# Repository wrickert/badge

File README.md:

<h2> BSidesIowa 2019 Badge </h2>
The badge for BSidesIowa 2019 conference is a penny piano running on an ESP32 microcontroller running micropython.
This badge is fully rechargeable and all that is required to program it is a micro usb cable. 

<h3> Micropython </h3>
The micropython REPL prompt can be accessed using a serial console running at 115200 baud. 
Documentation for micropython can be found here, https://docs.micropython.org/en/latest/esp32/quickref.html

<h3> To program </h3>
The badge can be programmed directly through the REPL prompt on the serial console. To load new files onto the ESP32, first access the serial console and press Ctrl+C to end the running program on the board. Then, exit the serial console and use ampy.py to load new programs. Instructions to install ampy can be found here, https://learn.adafruit.com/micropython-basics-load-files-and-run-code/install-ampy

Common ampy commands:<br>
To program the board: ampy -p /dev/ttyUSB0 put main.py

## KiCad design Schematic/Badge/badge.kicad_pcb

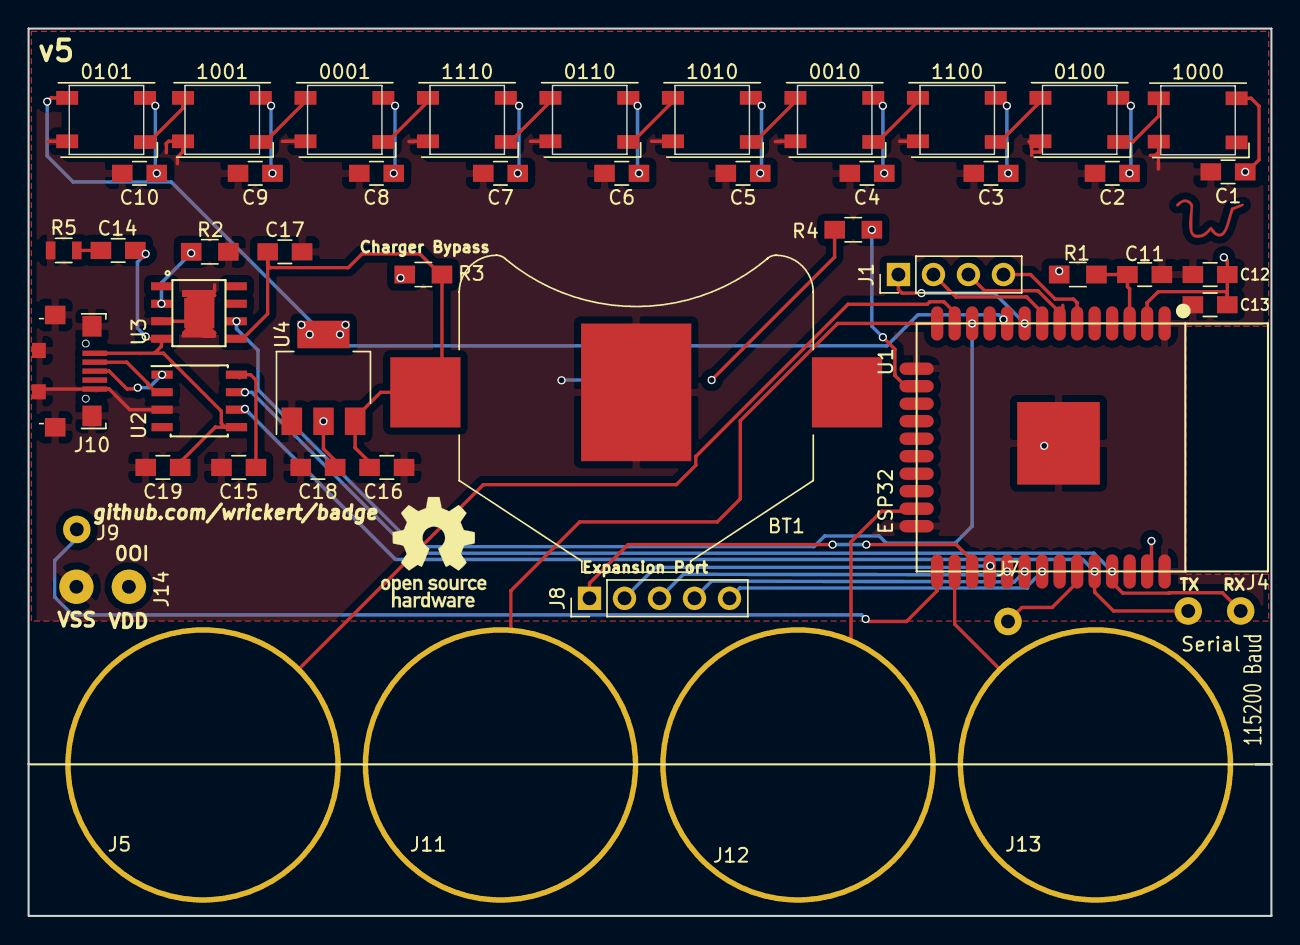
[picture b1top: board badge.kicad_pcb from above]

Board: 2 copper layers, 90.2 x 64.4 mm, 52 parts (1 on the bottom side), 40 nets.

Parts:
0001, 0010, 0100, 0101, 0110, 1000, 1001, 1010, 1100, 1110: WS2812B; WS2812B-Sunken
BT1: Battery_Cell; Keystone_3008_1x2450-CoinCell
C1, C2, C3, C4, C5, C6, C7, C8, C9, C10, C11, C12, C15, C19: 0.1uF; C_0805_HandSoldering
C13, C14, C17: 10uF; C_0805_HandSoldering
C16, C18: 1uF; C_0805_HandSoldering
J1: Left2; Pin_Header_Straight_1x04_Pitch2.54mm
J4: Serial; SolderWirePad_2x_1mmDrill
J5: Penny3; Penny
J7: Right2; SolderWirePad_single_1mmDrill
J8: Right3; Pin_Header_Straight_1x05_Pitch2.54mm
J9: Right4; SolderWirePad_single_1mmDrill
J10: USB_B_Micro; USB_Micro-B_Jing
J11: Penny2; Penny
J12: Penny1; Penny
J13: Penny0; Penny
J14: Power; SolderWirePad_2x_1mmDrill
LS1: PKMCS0909E4000-R1; XDCR_PKMCS0909E4000-R1
R1: 10k; R_0805_HandSoldering
R2: 1k; R_0805_HandSoldering
R3: 0ohm; R_0805_HandSoldering
R4: 22ohm; R_0805_HandSoldering
R5: 1.5; R_0805
Ref**: Val**; W
U1: ESP32-WROOM
U2: otter_CH330; SOIC-8_3.9x4.9mm_Pitch1.27mm
U3: HX4056
U4: TLV1117-33; SOT-223-3_TabPin2

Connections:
IO0: J9.1, U1.25
IO5: J8.3, U1.29
IO13: R4.1, U1.16
IO16: J8.1, U1.27
IO17: J8.2, U1.28
IO18: J8.4, U1.30
IO19: J8.5, U1.31
IO21: J7.1, U1.33
IO27: U1.12, U3.6
IO32: J1.2, U1.8
IO33: J1.1, U1.9
IO34: J1.4, U1.6
IO35: J1.3, U1.7
unnamed: C11.1, R1.2, U1.3
unnamed: C14.1, R5.2
unnamed: C15.1, U2.8
unnamed: J10.2, U2.2
unnamed: J10.3, U2.1
unnamed: 0100.4, 1000.2
unnamed: 0100.2, 1100.4
unnamed: 0010.4, 1100.2
unnamed: 0010.2, 1010.4
unnamed: 0110.4, 1010.2
unnamed: 0110.2, 1110.4
unnamed: 0001.4, 1110.2
unnamed: 0001.2, 1001.4
unnamed: 0101.4, 1001.2
unnamed: LS1.1, R4.2
unnamed: R2.1, U3.2
P0: J13.1, U1.26
P1: J12.1, U1.23
P2: J11.1, U1.14
P3: J5.1, U1.13
RX: J4.1, U1.35, U2.7
SPI: 0101.2, U1.10
TX: J4.1, U1.34, U2.6
VBUS: C14.2, C19.2, J10.1, U2.5, U3.4
VDD: 0001.1, 0010.1, 0100.1, 0101.1, 0110.1, 1000.1, 1001.1, 1010.1, 1100.1, 1110.1, C1.1, C2.1, C3.1, C4.1, C5.1, C6.1, C7.1, C8.1, C9.1, C10.1, C12.2, C13.2, C18.1, J14.1, R1.1, R3.1, U1.2, U4.2
VDDA: BT1.1, C16.1, C17.2, R3.2, U3.5, U4.3
VSS: 0001.3, 0010.3, 0100.3, 0101.3, 0110.3, 1000.3, 1001.3, 1010.3, 1100.3, 1110.3, BT1.2, C1.2, C2.2, C3.2, C4.2, C5.2, C6.2, C7.2, C8.2, C9.2, C10.2, C11.2, C12.1, C13.1, C15.2, C16.2, C17.1, C18.2, C19.1, J10.5, J10.6, J14.1, LS1.2, R2.2, R5.1, U1.1, U1.15, U1.24, U1.38, U1.39, U2.3, U3.3, U3.9, U4.1

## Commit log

2018-04-16 First commit with work piano code
2018-04-16 First commit with work piano code, actually included this time
2018-04-16 Added todo and better note selection, thanks to Alex
2018-04-17 Keys and rainbow working
2018-04-17 Added prismPiano
2018-05-13 Added schematic
2018-05-14 Finished v1 schematic
2018-05-14 Changed pin for speaker and added schematic symbol
2018-05-14 Checking for update
2018-06-05 New board revision
2018-06-05 New board revision - power pins again
2018-06-12 Fixed pizeo and power screen printing
2019-01-04 vallen says hi
2019-01-05 Housekeeping
2019-01-10 Added charging hardware
2019-01-13 Ordered V3
2019-01-13 Added bom
2019-01-19 Ordered v3 from pcbway
2019-01-19 Created bom
2019-01-31 Fixed issues with v3, rearranged caps to make assembly eaiser
2019-02-20 v4, changes to add all of the best chineseium bits I can find
2019-04-06 v5 arrived
2019-04-12 Oh we oh, oh-we-oh
2019-04-12 Better labeling
2019-04-12 Squashing bugs
2019-04-12 Added to readme
2019-04-12 Added the Pokemon Red/Blue theme
    I'm not happy with how it sounds. This song is a bit too low and
    brooding for this hardware, and the timing is a bitch.
    May want to look into other songe. Something a bit happier.
    Also need to add lights.
2019-04-13 Added try catch
2019-04-13 Added silent reboot for value error
2019-04-13 Better colors
2019-04-15 I can now play the original theme from the Legend of Zelda: Links Awakening
    The
2019-04-15 Added dimming display to improve battery life
2019-04-16 Changing times
2019-04-16 Improved battery life
2019-04-16 bug fix
2019-04-20 Added to readme and party mode
2019-04-22 Create imperialmarch.main.py
    Imperial March for the badge.
2019-04-22 Create mario.main.py
    This is the Mario theme for use with the badge.
